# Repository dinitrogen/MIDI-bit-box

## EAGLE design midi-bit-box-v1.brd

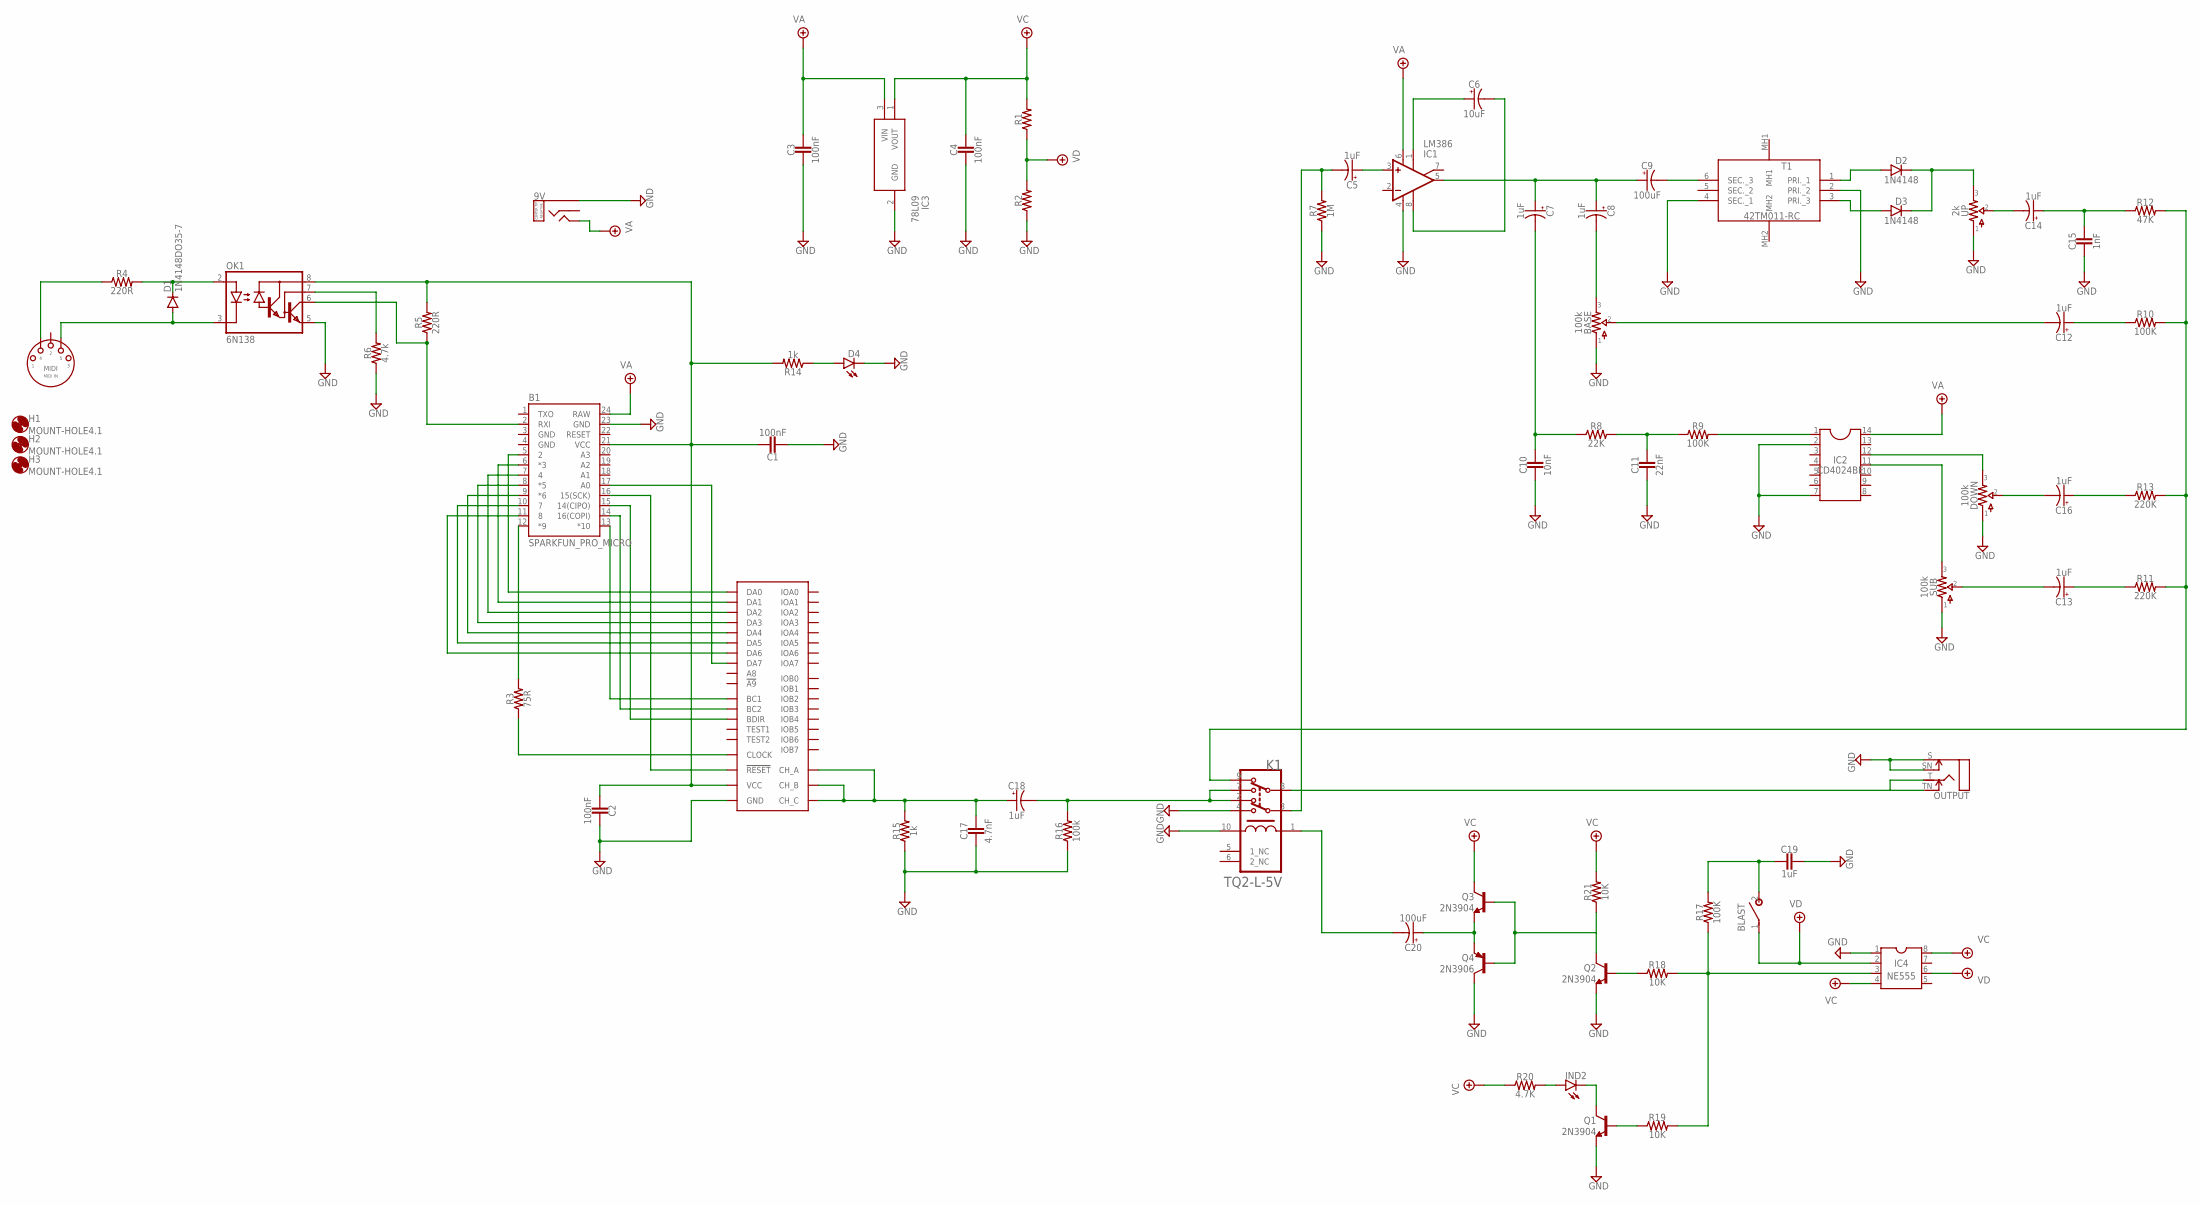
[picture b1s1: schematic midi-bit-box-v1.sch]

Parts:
9V: DC_TRS_PADS; DC_TRS
B1: SPARKFUN_PRO_MICRO
BASE: 100k; TRIM1
BLAST: SPST; SPST.WIRE
C1, C2, C3, C4: 100nF; 0.2".SML
C5, C7, C8, C12, C13, C14, C16, C18: 1uF; 0502
C6: 10uF; 0502
C9, C20: 100uF; 0502
C10: 10nF; 0.2".SML
C11: 22nF; 0.2".SML
C15: 1nF; 0.2".SML
C17: 4.7nF; 0.2".SML
C19: 1uF; 0.2".LRG
D1: 1N4148DO35-7; DO35-7
D2, D3: 1N4148; DO41-3
D4: LED.2; 3MM_1
DOWN: 100k; TRIM1
H1, H2, H3: MOUNT-HOLE4.1; 4,1
IC1: LM386; DIP08
IC2: CD4024BE; DIP14.1
IC3: 78L09; L78L09ACZTR
IC4: NE555; DIP08
IND2: 5MM_LED; 3MM_1
K1: PANASONIC_TQ2-L-5VPANASONIC_TQ2-L-5V_0_0; PANASONIC_TQ2-L-5V_0
MIDI: MIDI IN; 3PADS
OK1: 6N138; DIL08
OUTPUT: SWITCHED_MONO_PADS; 4PADS
Q1, Q2, Q3: 2N3904; TO92
Q4: 2N3906; TO92
R1, R2: R.3B; 0.3".B
R3: 75R; 0.3".B
R4, R5: 220R; 0.3".B
R6: 4.7k; 0.3".B
R7: 1M; 0.3".B
R8: 22K; 0.3".B
R9, R10, R17: 100K; 0.3".B
R11, R13: 220K; 0.3".B
R12: 47K; 0.3".B
R14, R15: 1k; 0.3".B
R16: 100k; 0.3".B
R18, R19, R21: 10K; 0.3".B
R20: 4.7K; 0.3".B
SUB: 100k; TRIM1
T1: 42TM011-RC; 42TM011RC
U1: AY-3-8910; DIP-40/600MIL
UP: 2k; TRIM1

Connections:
GND: 9V.PWR, B1.3 (GND), B1.4 (GND), B1.23 (GND), BASE.1, C1.2, C2.1, C3.2, C4.2, C10.2, C11.2, C15.2, C17.2, C19.1, D4.K (C), DOWN.1, IC1.4 (V-), IC2.2, IC2.7, IC3.2 (GND), IC4.1, K1.4, K1.10 (S-/R+), OK1.5 (GND), OUTPUT.S, OUTPUT.SN, Q1.3 (E), Q2.3 (E), Q4.1 (C), R2.1, R6.1, R7.1, R15.1, R16.1, SUB.1, T1.2 (PRI._2), T1.4 (SEC._1), U1.1 (GND), UP.1
unnamed: MIDI.T (4), R4.1
unnamed: D1.C, OK1.2 (A), R4.2
unnamed: D1.A, MIDI.S (5), OK1.3 (C)
unnamed: B1.21 (VCC), C1.1, C2.2, OK1.8 (VCC), R5.2, R14.2, U1.40 (VCC)
unnamed: OK1.7 (VB), R6.2
unnamed: B1.2 (RXI), OK1.6 (VO), R5.1
unnamed: IC4.3, R17.1, R18.2, R19.2
unnamed: K1.8, OUTPUT.T, OUTPUT.TN
unnamed: B1.12 (*9), R3.2
unnamed: R3.1, U1.22 (CLOCK)
unnamed: B1.16 (15(SCK)), U1.23 (!RESET)
unnamed: B1.5 (2), U1.37 (DA0)
unnamed: B1.6 (*3), U1.36 (DA1)
unnamed: B1.7 (4), U1.35 (DA2)
unnamed: B1.8 (*5), U1.34 (DA3)
unnamed: B1.9 (*6), U1.33 (DA4)
unnamed: B1.10 (7), U1.32 (DA5)
unnamed: B1.11 (8), U1.31 (DA6)
unnamed: B1.17 (A0), U1.30 (DA7)
unnamed: B1.13 (*10), U1.29 (BC1)
unnamed: B1.14 (16(COPI)), U1.28 (BC2)
unnamed: B1.15 (14(CIPO)), U1.27 (BDIR)
unnamed: BASE.2, C12.-
unnamed: C16.-, DOWN.2
unnamed: DOWN.3, IC2.12
unnamed: C5.+, IC1.3 (+IN)
unnamed: C6.+, IC1.1 (GAIN1)
unnamed: C6.-, IC1.8 (GAIN2)
unnamed: C7.+, C8.+, C9.+, IC1.5 (OUT)
unnamed: C9.-, T1.6 (SEC._3)
unnamed: D2.A, T1.1 (PRI._1)
unnamed: D3.A, T1.3 (PRI._3)
unnamed: BASE.3, C8.-
unnamed: C7.-, C10.1, R8.1
unnamed: C11.1, R8.2, R9.1
unnamed: IC2.11, SUB.3
unnamed: C13.-, SUB.2
unnamed: D4.A, R14.1
unnamed: C14.-, UP.2
unnamed: BLAST.2, C19.2, R17.2
unnamed: C12.+, R10.1
unnamed: C16.+, R13.1
unnamed: C13.+, R11.1
unnamed: D2.C, D3.C, UP.3
unnamed: C5.-, K1.3, R7.2
unnamed: C14.+, C15.1, R12.1
unnamed: C17.1, C18.+, R15.2, U1.3 (CH_B), U1.4 (CH_A), U1.38 (CH_C)
unnamed: IC2.1, R9.2
unnamed: IND2.A, R20.2
unnamed: Q2.1 (C), R21.1
unnamed: Q2.2 (B), R18.1
unnamed: Q1.2 (B), R19.1
unnamed: IND2.K (C), Q1.1 (C)
unnamed: C20.+, Q3.3 (E), Q4.3 (E)
unnamed: Q3.2 (B), Q4.2 (B)
unnamed: C20.-, K1.1 (S+/R-)
unnamed: C18.-, K1.2, K1.7, R16.2
unnamed: K1.9, R10.2, R11.2, R12.2, R13.2
VA: 9V.GND, B1.24 (RAW), C3.1, IC1.6 (V+), IC2.14, IC3.3 (VIN)
VC: C4.1, IC3.1 (VOUT), IC4.4, IC4.8, Q3.1 (C), R1.2, R20.1, R21.2
VD: BLAST.1, IC4.2, IC4.6, R1.1, R2.2

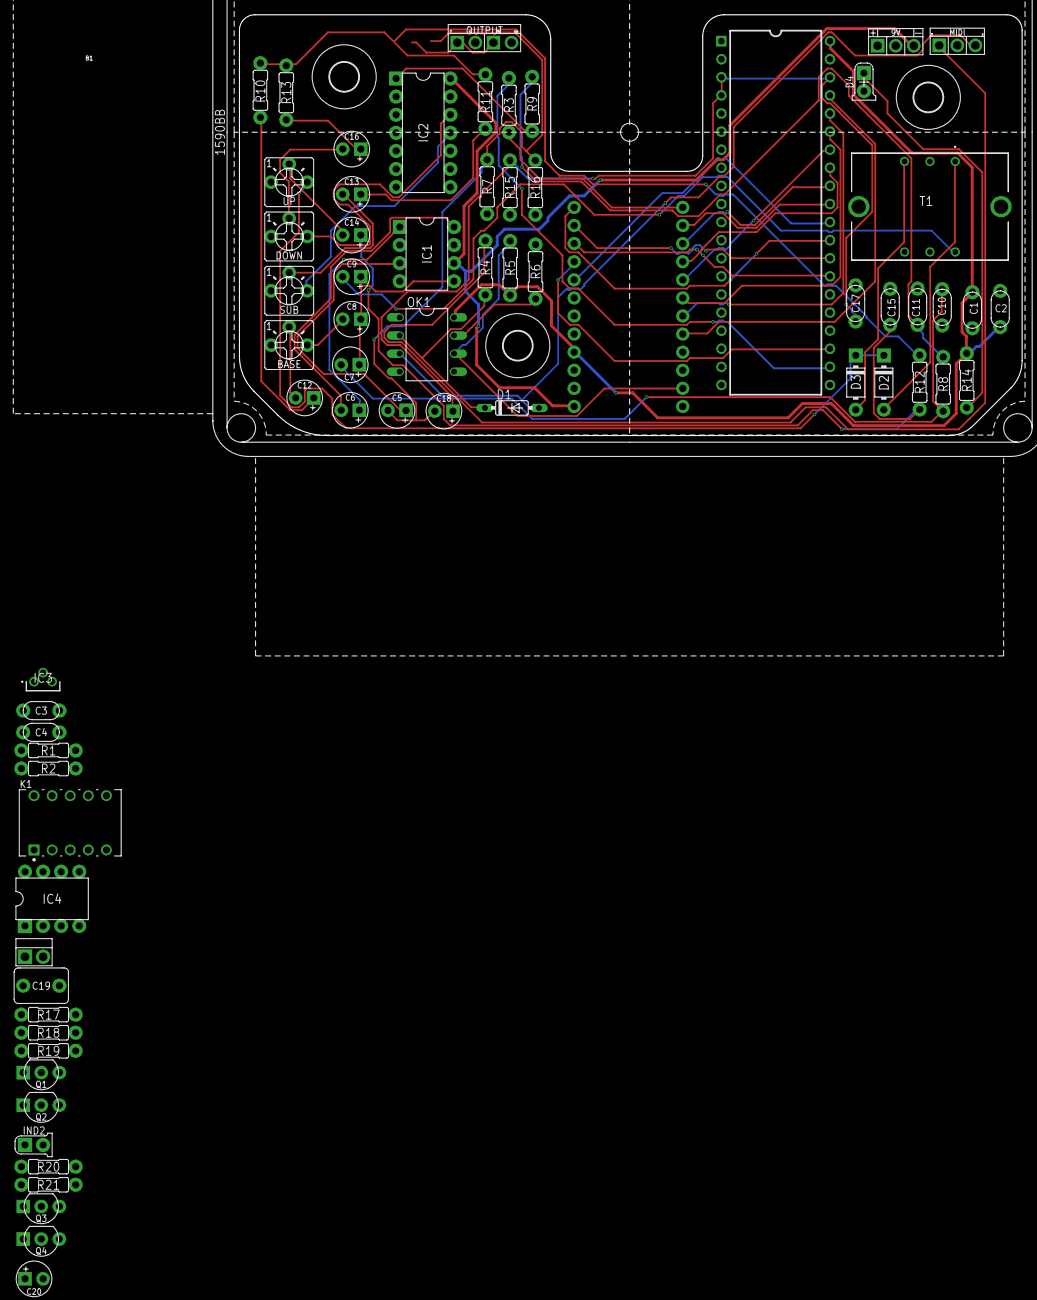
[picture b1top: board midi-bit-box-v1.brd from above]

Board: 2 copper layers, 109.9 x 59.1 mm, 71 parts (1 on the bottom side), 62 nets.

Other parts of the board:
U$1: 1590BB

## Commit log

2022-01-26 Added SPST and latching relay switching circuit
2022-02-03 Create kicad
2022-02-03 Create deleteme
2022-02-03 Add files via upload
    initial kicad uploads
2022-02-04 Add files via upload
    updated pwr/audio jacks and design rules
2022-02-05 added dual LED
2022-02-07 added trimpot to control output volume
2022-02-08 corrected DC input jack pads
2022-02-08 corrected DC input pad shapes
2022-02-23 enclosure graphic first draft
2022-02-24 added work-in-progress artwork
2022-02-24 updates to enclosure graphic
2022-02-27 draft print files
2022-04-13 Added sketch to test out different DSR envelopes
2022-05-01 Added gerbers
2022-05-01 no startup jingle

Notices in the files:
parts and their libraries:
SparkFun-Boards: Licensing: Creative Commons ShareAlike 4.0 International - https://creativecommons.org/licenses/by-sa/4.0
